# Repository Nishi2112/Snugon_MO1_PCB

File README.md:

C:\Users\B1401\OneDrive\Workspace\仕事\Snugon_MO1_PCB\Snugon_MO1_PCB

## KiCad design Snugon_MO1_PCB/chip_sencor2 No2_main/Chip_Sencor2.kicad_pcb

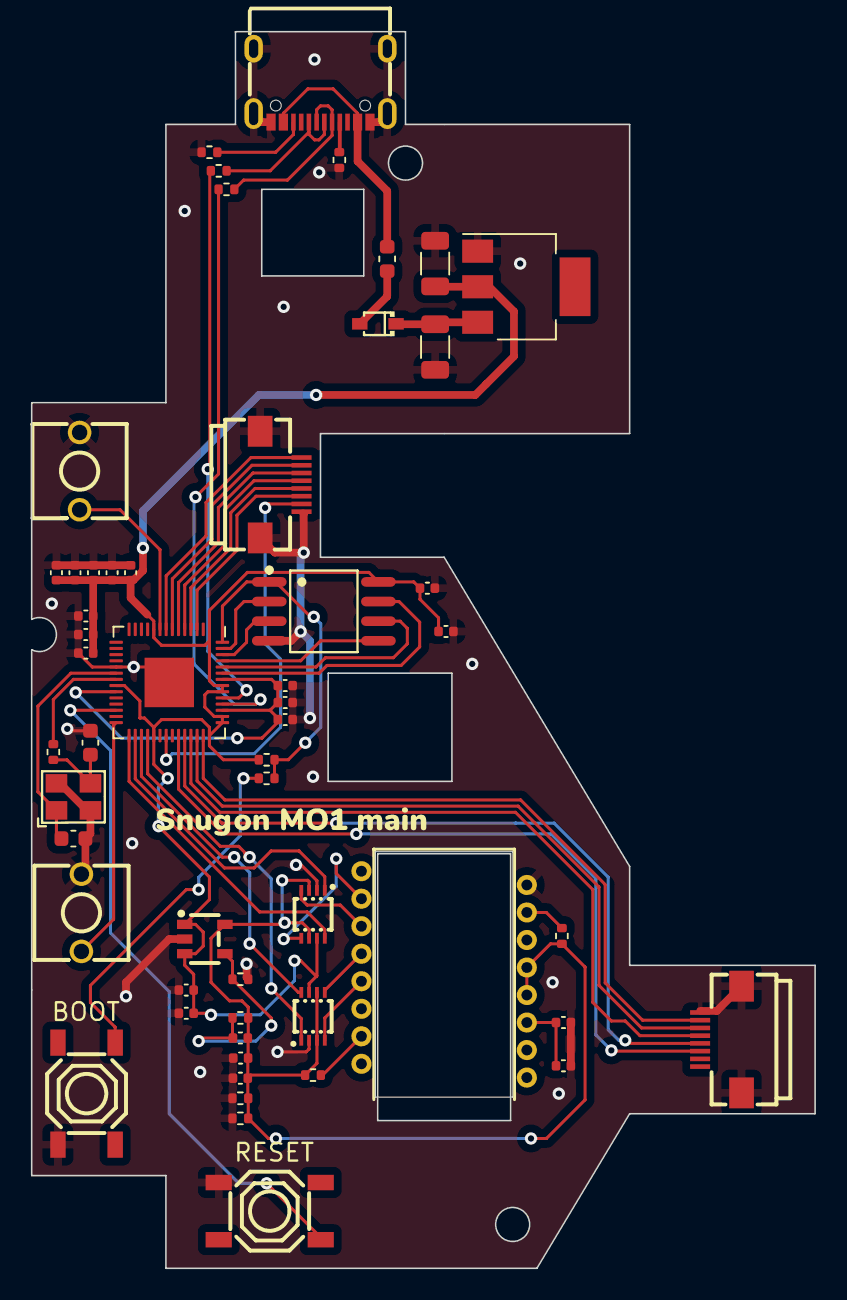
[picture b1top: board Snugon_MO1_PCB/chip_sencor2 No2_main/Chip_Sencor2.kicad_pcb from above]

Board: 2 copper layers, 50.7 x 80.0 mm, 54 parts (0 on the bottom side), 50 nets.

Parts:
C1, C4, C5: 10uF; C_0402_1005Metric
C2, C3, C6, C7, C16, C17, C18, C19, C20, C21, C22, C23, C24, C27: 100nF; C_0402_1005Metric
C8, C9: 30pF; C_0603_1608Metric
C14, C15: 10uF; C_1206_3216Metric
C25, C26, C28: 2.2uF; C_0402_1005Metric
F2: Fuse; Fuse_0603_1608Metric
J1, J6: Conn_01x8_Pin + 2; FFCｺﾈｸﾀ_FPC-SMD_P0.50-8P_FGS-XJ-H2.0
J3: USB_C_Receptacle_USB2.0; USB-C-SMD_TYPE-C-6PIN-2MD-073
R1: 37.4k; R_0402_1005Metric
R2: 63.4k; R_0402_1005Metric
R3, R4, R6, R14: 10k; R_0402_1005Metric
R5: 39; R_0402_1005Metric
R8, R9: 5.1k; R_0402_1005Metric
R10, R11: 27; R_0402_1005Metric
R13, R15: 1k; R_0402_1005Metric
SD1: Schottky diode; 1N5819WS_C191023
SW0, SW1: SW_PUSH; SW-TH_L6.2-W6.2-P5.00
SW14: BOOT; SW-SMD_4P-L5.1-W5.1-P3.70-LS6.5-TL-2
SW15: RESET; SW-SMD_4P-L5.1-W5.1-P3.70-LS6.5-TL-2
U1: RP2040; QFN-56-1EP_7x7mm_P0.4mm_EP3.2x3.2mm
U2: TPS73601DBV; TPS73601DBVR C59200
U3, U4: TXS0102DCU; TXS0102DCUR C53434
U5: PMW3360DM-T2QU; PMW3360
U7: NCP1117-3.3_SOT223; SOT-223
U8: W25Q128JVSIQ; W25Q128JVSIQ_C97521
Y1: 12MHz; X322512MSB4SI_C9002

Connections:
+1V1: C16.1, C17.1, C25.1, U1.23 (DVDD), U1.45 (VREG_VOUT), U1.50 (DVDD)
+3V3: C1.1, C2.1, C15.1, C18.1, C19.1, C20.1, C21.1, C22.1, C23.1, C24.1, C26.1, C27.1, C28.1, R14.1, U1.1 (IOVDD), U1.10 (IOVDD), U1.22 (IOVDD), U1.33 (IOVDD), U1.42 (IOVDD), U1.43 (ADC_AVDD), U1.44 (VREG_IN), U1.48 (USB_VDD), U1.49 (IOVDD), U2.1 (IN), U2.3 (EN), U3.7 (VCCB), U4.7 (VCCB), U7.2 (VO), U8.8 (VCC)
+5V: C14.1, SD1.1 (K), U7.3 (VI)
D+: R11.1, U1.47 (USB_DP)
D-: R10.1, U1.46 (USB_DM)
GND: C1.2, C2.2, C4.2, C5.2, C6.2, C7.2, C8.2, C9.2, C14.2, C15.2, C16.2, C17.2, C18.2, C19.2, C20.2, C21.2, C22.2, C23.2, C24.2, C25.2, C26.2, C27.2, C28.2, J1.1, J1.9, J1.10, J3.1 (GND), J3.12 (GND), J3.13 (SHIELD), J3.14 (SHIELD), J6.1, J6.9, J6.10, R2.2, R3.2, R4.2, R8.1, R9.1, SW0.1, SW1.1, SW14.1, SW15.1, U1.19 (TESTEN), U1.57 (GND), U2.2 (GND), U3.2 (GND), U4.2 (GND), U5.8 (GND), U7.1 (GND), U8.4 (GND), Y1.2, Y1.4
MISO: U1.31 (GPIO20), U4.8 (B1)
MISO1.9V: U4.5 (A1), U5.12 (MISO)
MOSI: U1.30 (GPIO19), U3.1 (B2)
MOSI1.9V: U3.4 (A2), U5.11 (MOSI)
NCS: U1.32 (GPIO21), U4.1 (B2)
NCS1.9V: U4.4 (A2), U5.13 (~CS)
unnamed: C9.1, R15.1, Y1.3
unnamed: J3.4 (CC1), R8.2
unnamed: J3.10 (CC2), R9.2
unnamed: J3.6 (D+), J3.8 (D+), R11.2
unnamed: J3.5 (D-), J3.7 (D-), R10.2
unnamed: F2.2, SD1.2 (A)
unnamed: C8.1, U1.20 (XIN), Y1.1
unnamed: R15.2, U1.21 (XOUT)
unnamed: C3.2, R1.2, R2.1, U2.4 (FB)
unnamed: C3.1, C4.1, C7.1, R1.1, R3.1, R4.1, R5.2, R6.1, U2.5 (OUT), U3.3 (VCCA), U3.6 (OE), U4.3 (VCCA), U4.6 (OE), U5.4 (VDD), U5.5 (VDDIO)
unnamed: R5.1, U5.15 (LED_P)
unnamed: C5.1, C6.1, U5.3 (VDDPIX)
unnamed: R6.2, U5.7 (~RESET)
QSPI_SCLK: U1.52 (QSPI_SCLK), U8.6 (CLK)
QSPI_SD0: U1.53 (QSPI_SD0), U8.5 (DI(IO0))
QSPI_SD1: U1.55 (QSPI_SD1), U8.2 (DO(IO1))
QSPI_SD2: U1.54 (QSPI_SD2), U8.3 (IO2)
QSPI_SD3: U1.51 (QSPI_SD3), U8.7 (IO3)
QSPI_SS: R13.2, R14.2, U1.56 (QSPI_SS), U8.1 (~CS)
RE0A: J1.3, U1.3 (GPIO1)
RE0B: J1.2, U1.35 (GPIO23)
RESET: SW15.4 (A), U1.26 (RUN)
SCLK: U1.29 (GPIO18), U3.8 (B1)
SCLK1.9V: U3.5 (A1), U5.10 (SCLK)
SW0: SW0.2, U1.28 (GPIO17)
SW1: SW1.2, U1.9 (GPIO7)
SW2: J1.8, U1.8 (GPIO6)
SW3: J1.7, U1.7 (GPIO5)
SW4: J1.6, U1.6 (GPIO4)
SW5: J1.5, U1.5 (GPIO3)
SW6: J1.4, U1.4 (GPIO2)
SW7: J6.2, U1.41 (GPIO29_ADC3)
SW8: J6.3, U1.40 (GPIO28_ADC2)
SW9: J6.4, U1.39 (GPIO27_ADC1)
SW10: J6.5, U1.38 (GPIO26_ADC0)
SW11: J6.6, U1.37 (GPIO25)
USB_BOOT: R13.1, SW14.4 (A)
VBUS: F2.1, J3.2 (VBUS), J3.11 (VBUS)

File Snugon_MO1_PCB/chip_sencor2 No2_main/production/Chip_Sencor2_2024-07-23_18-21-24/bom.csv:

Designator,Footprint,Quantity,Value,LCSC Part #
BOOT,SW-SMD_4P-L5.1-W5.1-P3.70-LS6.5-TL-2,1,BOOT,C318884
"C1, C4, C5",0402,3,10uF,C15525
"C14, C15",1206,2,10uF,C13585
"C16, C17, C18, C19, C2, C20, C21, C22, C23, C24, C27, C3, C6, C7",0402,14,100nF,C1525
"C25, C26, C28",0402,3,2.2uF,C12530
"C8, C9",0603,2,30pF,C1658
F2,0603,1,Fuse,C187605
"J1, J6",FFCｺﾈｸﾀ_FPC-SMD_P0.50-8P_FGS-XJ-H2.0,2,Conn_01x8_Pin + 2,C262264
J3,USB-C-SMD_TYPE-C-6PIN-2MD-073,1,USB_C_Receptacle_USB2.0,C2765186
R1,0402,1,37.4k,C25888
"R10, R11",0402,2,27,C25100
"R13, R15",0402,2,1k,C11702
"R14, R3, R4, R6",0402,4,10k,C25744
R2,0402,1,63.4k,C38606
R5,0402,1,39,C185420
"R8, R9",0402,2,5.1k,C25905
RST,SW-SMD_4P-L5.1-W5.1-P3.70-LS6.5-TL-2,1,RESET,C318884
SD1,1N5819WS_C191023,1,SD1,C191023
"SW0, SW1",SW-TH_L6.2-W6.2-P5.00,2,SW_PUSH,C400268
U1,QFN-56-1EP_7x7mm_P0.4mm_EP3.2x3.2mm,1,RP2040,C2040
U2,TPS73601DBVR C59200,1,TPS73601DBV,C59200
"U3, U4",TXS0102DCUR C53434,2,TXS0102DCU,C53434
U5,PMW3360,1,PMW3360DM-T2QU,C20612443
U7,SOT-223,1,NCP1117-3.3_SOT223,C6186
U8,W25Q128JVSIQ_C97521,1,U8,C97521
Y1,X322512MSB4SI_C9002,1,Y1,C9002

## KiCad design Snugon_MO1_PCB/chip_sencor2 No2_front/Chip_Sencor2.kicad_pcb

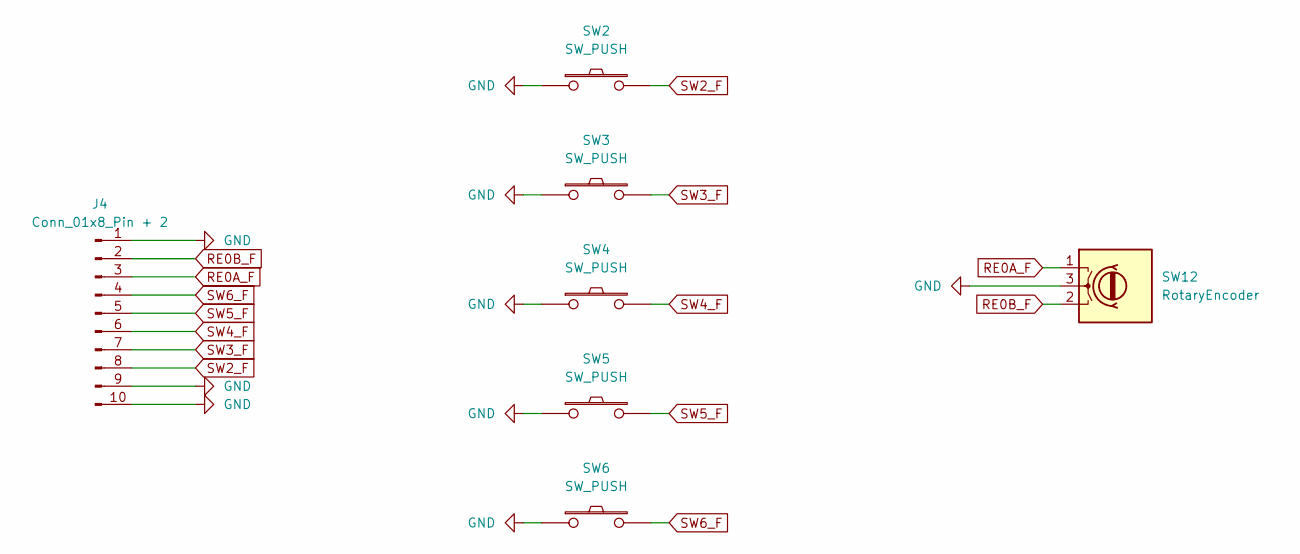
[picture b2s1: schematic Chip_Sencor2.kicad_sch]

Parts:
J4: Conn_01x8_Pin + 2; FFCｺﾈｸﾀ_FPC-SMD_P0.50-8P_FGS-XJ-H2.0; LCSC C262264
SW2, SW3, SW4, SW5, SW6: SW_PUSH; SW-TH_L6.2-W6.2-P5.00
SW12: RotaryEncoder; SW-TH_CEN971112R02

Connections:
GND: J4.1, J4.9, J4.10, SW2.1, SW3.1, SW4.1, SW5.1, SW6.1, SW12.3
RE0A_F: J4.3, SW12.1 (A)
RE0B_F: J4.2, SW12.2
SW2_F: J4.8, SW2.2
SW3_F: J4.7, SW3.2
SW4_F: J4.6, SW4.2
SW5_F: J4.5, SW5.2
SW6_F: J4.4, SW6.2

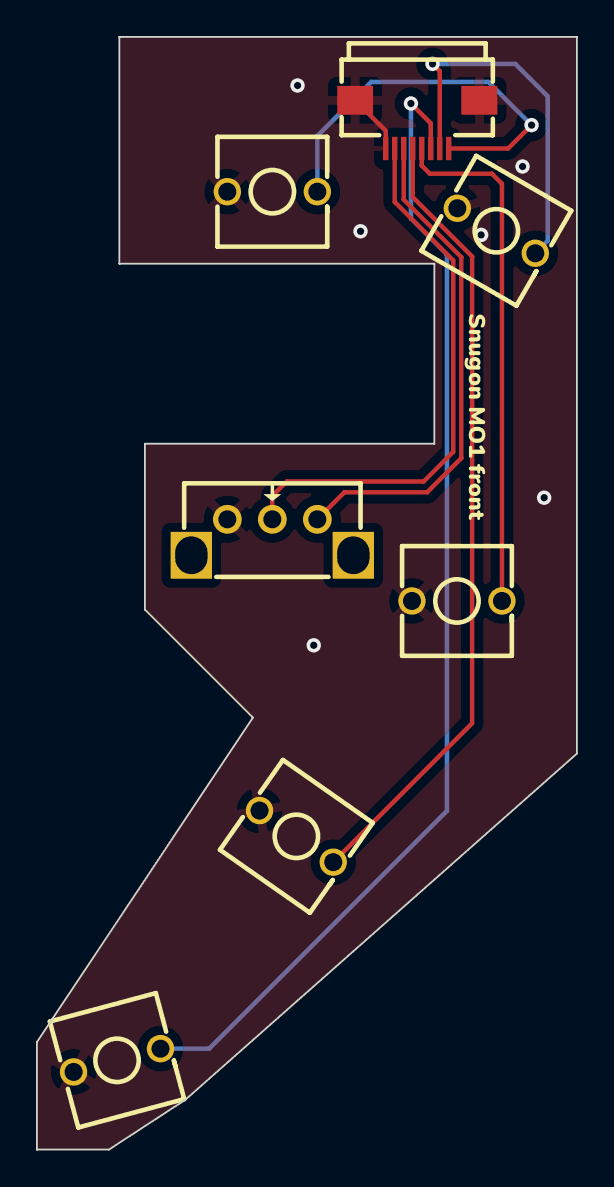
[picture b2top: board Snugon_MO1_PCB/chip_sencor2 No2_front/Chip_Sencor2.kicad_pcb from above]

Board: 2 copper layers, 30.0 x 61.8 mm, 7 parts (0 on the bottom side), 8 nets.

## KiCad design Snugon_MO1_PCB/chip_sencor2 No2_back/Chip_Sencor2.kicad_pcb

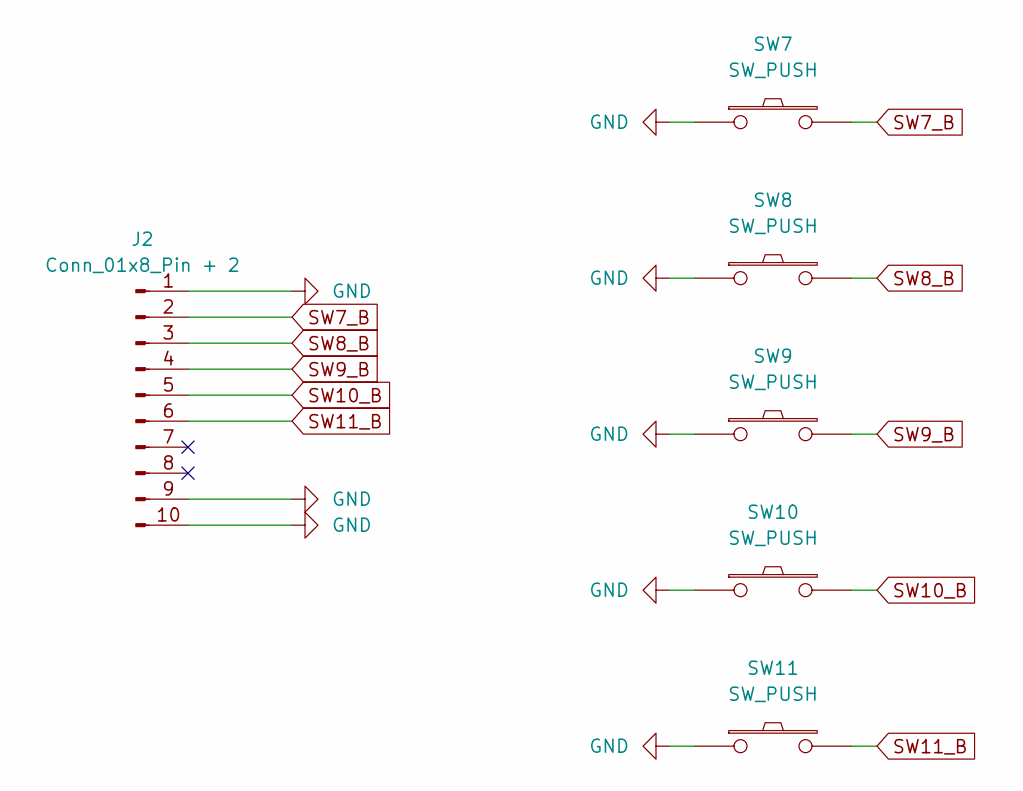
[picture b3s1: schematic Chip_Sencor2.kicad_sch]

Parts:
J2: Conn_01x8_Pin + 2; FFCｺﾈｸﾀ_FPC-SMD_P0.50-8P_FGS-XJ-H2.0; LCSC C262264
SW7, SW8, SW9, SW10, SW11: SW_PUSH; SW-TH_L6.2-W6.2-P5.00

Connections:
GND: J2.1, J2.9, J2.10, SW7.1, SW8.1, SW9.1, SW10.1, SW11.1
SW7_B: J2.2, SW7.2
SW8_B: J2.3, SW8.2
SW9_B: J2.4, SW9.2
SW10_B: J2.5, SW10.2
SW11_B: J2.6, SW11.2

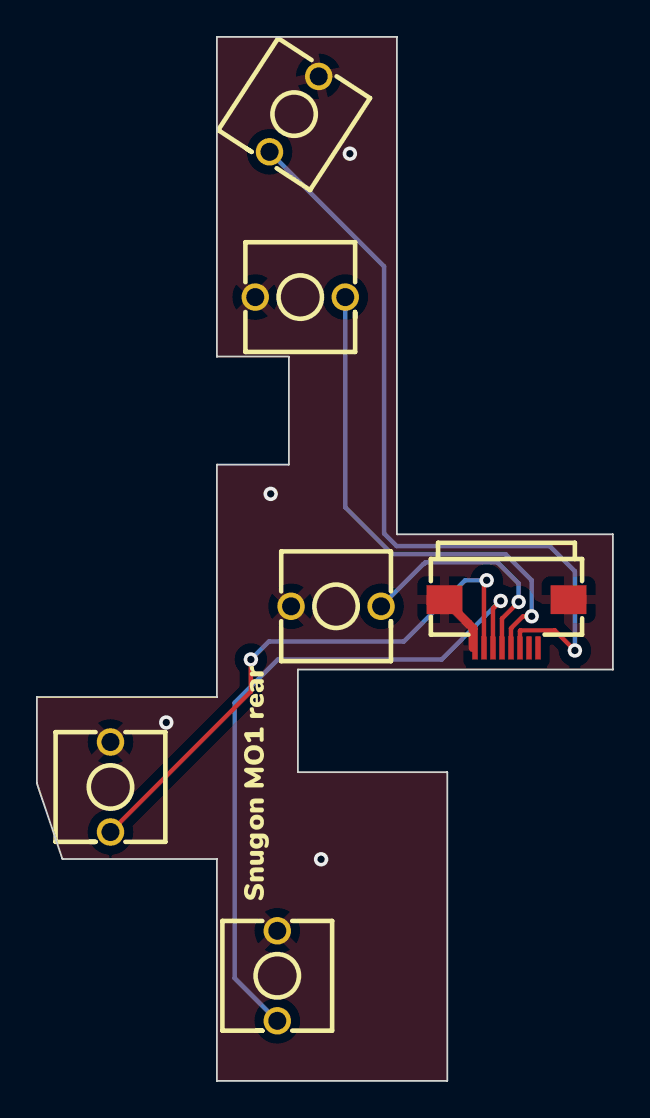
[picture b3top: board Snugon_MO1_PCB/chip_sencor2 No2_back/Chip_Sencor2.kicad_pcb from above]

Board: 2 copper layers, 32.0 x 58.0 mm, 6 parts (0 on the bottom side), 6 nets.

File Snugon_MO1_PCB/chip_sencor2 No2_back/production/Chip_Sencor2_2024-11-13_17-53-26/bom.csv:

Designator,Footprint,Quantity,Value,LCSC Part #
J2,FFCｺﾈｸﾀ_FPC-SMD_P0.50-8P_FGS-XJ-H2.0,1,Conn_01x8_Pin + 2,C262264
"SW10, SW11, SW7, SW8, SW9",SW-TH_L6.2-W6.2-P5.00,5,SW_PUSH,C400268

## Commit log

2024-11-13 Initial commit: 既存のプロジェクトファイルを追加
2024-11-13 README追加
2024-11-13 リセットボタンとブートボタンの配線修正
2024-11-14 スイッチとエンコーダーはPCBAしない
2024-12-26 エンコーダの配線修正
